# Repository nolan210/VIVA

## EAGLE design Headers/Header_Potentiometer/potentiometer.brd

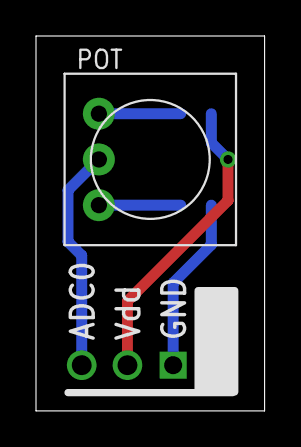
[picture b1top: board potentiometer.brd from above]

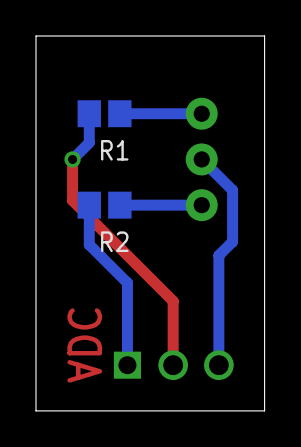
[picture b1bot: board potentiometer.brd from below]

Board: 2 copper layers, 12.7 x 20.8 mm, 4 parts (2 on the bottom side), 5 nets.

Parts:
POT: TRIM-3386
R1, R2: R0805
U$1: VIVA-HEADER-ADC-1; VIVA-HEADER-ADC-RA-2

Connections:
ADC: POT.2, U$1.3
GND: R2.1, U$1.1
unnamed: POT.1, R1.1
unnamed: POT.3, R2.2
VDD: R1.2, U$1.2

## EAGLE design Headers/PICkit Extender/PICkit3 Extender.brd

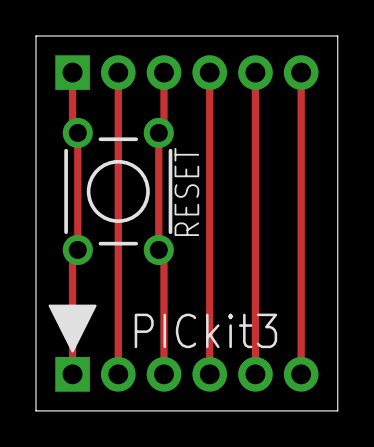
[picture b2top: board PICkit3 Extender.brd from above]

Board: 2 copper layers, 16.8 x 20.8 mm, 3 parts (0 on the bottom side), 6 nets.

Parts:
RESET: TL1105
U$1: PICKIT3; PINS_6_PICKIT3
U$3: PICKIT3PLAIN; PINS_6

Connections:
unnamed: RESET.2, RESET.4, U$1.1, U$3.1
unnamed: U$1.2, U$3.2
unnamed: RESET.1, RESET.3, U$1.3, U$3.3
unnamed: U$1.4, U$3.4
unnamed: U$1.5, U$3.5
unnamed: U$1.6, U$3.6

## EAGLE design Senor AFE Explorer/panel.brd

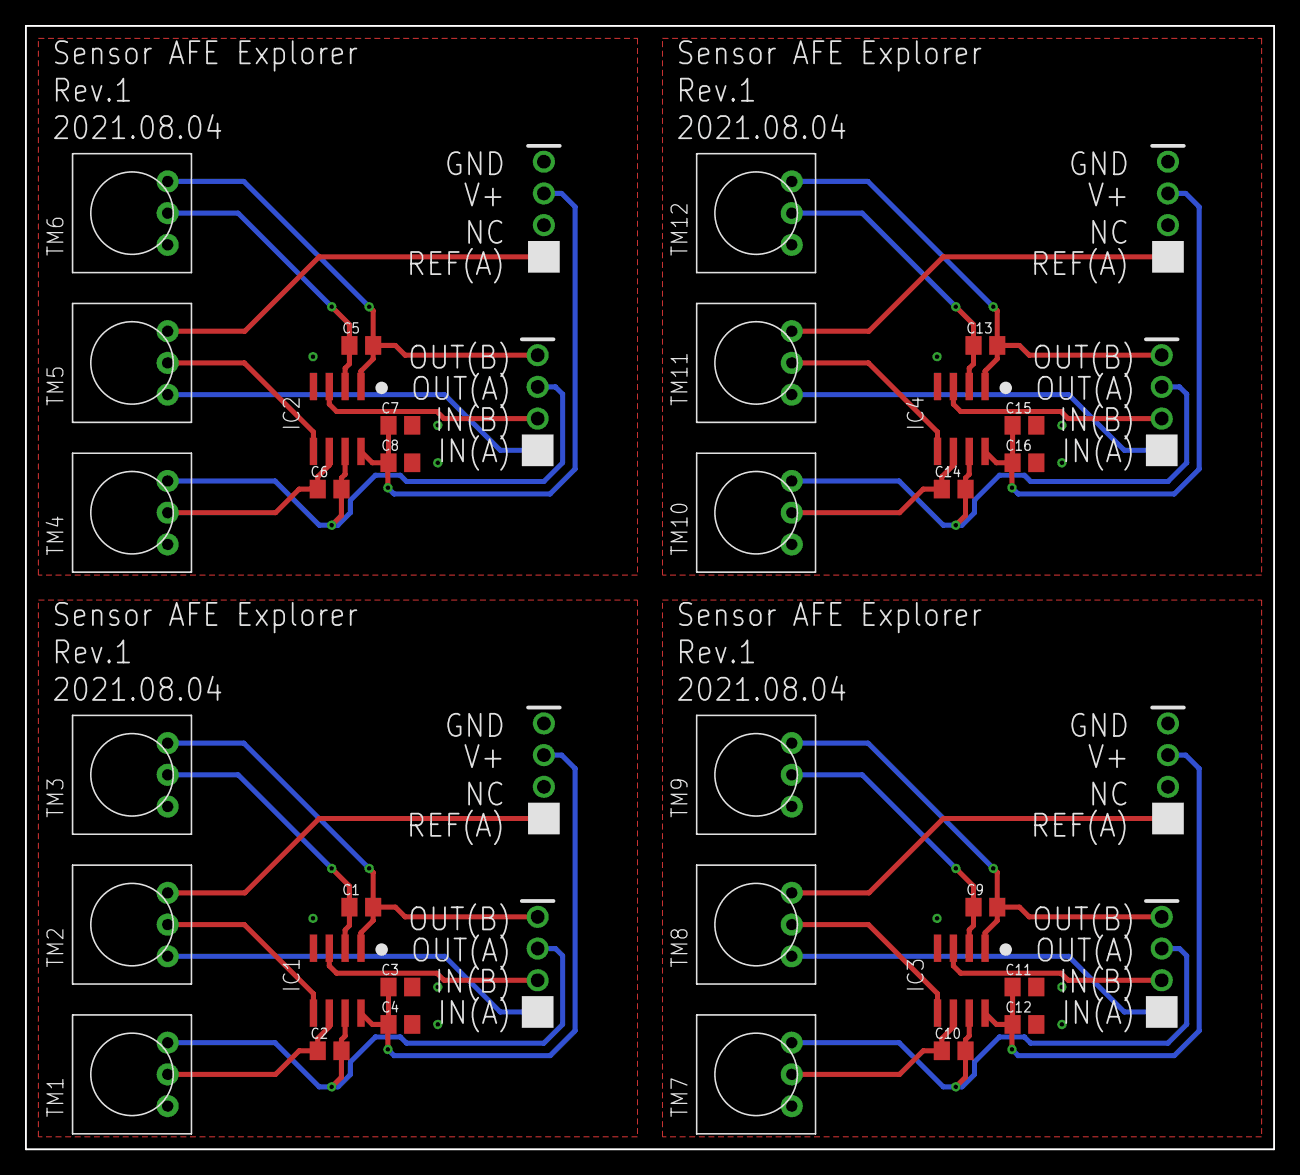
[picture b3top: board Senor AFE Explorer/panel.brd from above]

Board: 2 copper layers, 100.0 x 90.0 mm, 40 parts (0 on the bottom side), 40 nets.

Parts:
C1, C2, C3, C4, C5, C6, C7, C8, C9, C10, C11, C12, C13, C14, C15, C16: C0805
IC1, IC2, IC3, IC4: AD8542R; SO8
TM1, TM2, TM3, TM4, TM5, TM6, TM7, TM8, TM9, TM10, TM11, TM12: TRIM-3386
U$1, U$2, U$3, U$4, U$5, U$6, U$7, U$8: PINS_4SILK; PCB_4

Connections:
GND: C3.2, C4.2, IC1.4, TM1.1, TM3.1, U$2.P$4
GND1: C7.2, C8.2, IC2.4, TM4.1, TM6.1, U$4.P$4
GND2: C11.2, C12.2, IC3.4, TM7.1, TM9.1, U$6.P$4
GND3: C15.2, C16.2, IC4.4, TM10.1, TM12.1, U$8.P$4
unnamed: C2.1, IC1.6, TM1.2
unnamed: C2.2, IC1.7, TM1.3, U$1.P$3
unnamed: C1.1, IC1.2, TM3.2
unnamed: C1.2, IC1.1, TM3.3, U$1.P$4
unnamed: IC1.3, U$1.P$2
unnamed: TM2.1, U$1.P$1
unnamed: IC1.5, TM2.2
unnamed: TM2.3, U$2.P$1
unnamed: C6.1, IC2.6, TM4.2
unnamed: C6.2, IC2.7, TM4.3, U$3.P$3
unnamed: C5.1, IC2.2, TM6.2
unnamed: C5.2, IC2.1, TM6.3, U$3.P$4
unnamed: IC2.3, U$3.P$2
unnamed: TM5.1, U$3.P$1
unnamed: IC2.5, TM5.2
unnamed: TM5.3, U$4.P$1
unnamed: C10.1, IC3.6, TM7.2
unnamed: C10.2, IC3.7, TM7.3, U$5.P$3
unnamed: C9.1, IC3.2, TM9.2
unnamed: C9.2, IC3.1, TM9.3, U$5.P$4
unnamed: IC3.3, U$5.P$2
unnamed: TM8.1, U$5.P$1
unnamed: IC3.5, TM8.2
unnamed: TM8.3, U$6.P$1
unnamed: C14.1, IC4.6, TM10.2
unnamed: C14.2, IC4.7, TM10.3, U$7.P$3
unnamed: C13.1, IC4.2, TM12.2
unnamed: C13.2, IC4.1, TM12.3, U$7.P$4
unnamed: IC4.3, U$7.P$2
unnamed: TM11.1, U$7.P$1
unnamed: IC4.5, TM11.2
unnamed: TM11.3, U$8.P$1
VCC: C3.1, C4.1, IC1.8, U$2.P$3
VCC1: C7.1, C8.1, IC2.8, U$4.P$3
VCC2: C11.1, C12.1, IC3.8, U$6.P$3
VCC3: C15.1, C16.1, IC4.8, U$8.P$3

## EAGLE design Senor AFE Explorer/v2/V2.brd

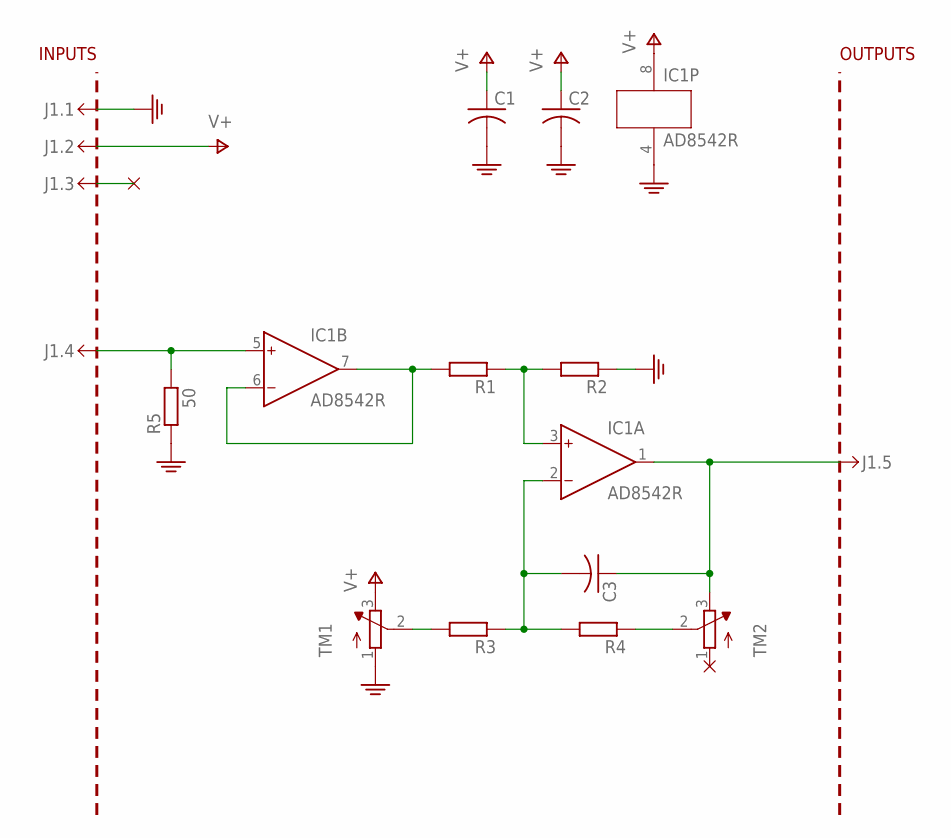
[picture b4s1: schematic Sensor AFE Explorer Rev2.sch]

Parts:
C1, C2, C3: C-USC0805; C0805
IC1: AD8542R; SO8
J1.: MINIPCB_5P50X50; MINIPCB_50X50MM; PART_NUMBER AFE Explorer
R1, R2, R3, R4: RESISTORSMD; R0805
R5: 50; R0805
TM1, TM2: TRIMPOT3386; TRIM-3386

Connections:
GND: C1.2, C2.2, IC1.4 (V-), J1..1, R2.1, R5.1, TM1.1 (A)
unnamed: IC1.5 (IN+), J1..4, R5.2
unnamed: IC1.6 (IN-), IC1.7 (OUT), R1.2
unnamed: IC1.3 (IN+), R1.1, R2.2
unnamed: C3.2, IC1.2 (IN-), R3.1, R4.2
unnamed: R3.2, TM1.2 (S)
unnamed: R4.1, TM2.2 (S)
unnamed: C3.1, IC1.1 (OUT), J1..5, TM2.3 (E)
V+: C1.1, C2.1, IC1.8 (V+), J1..2, TM1.3 (E)

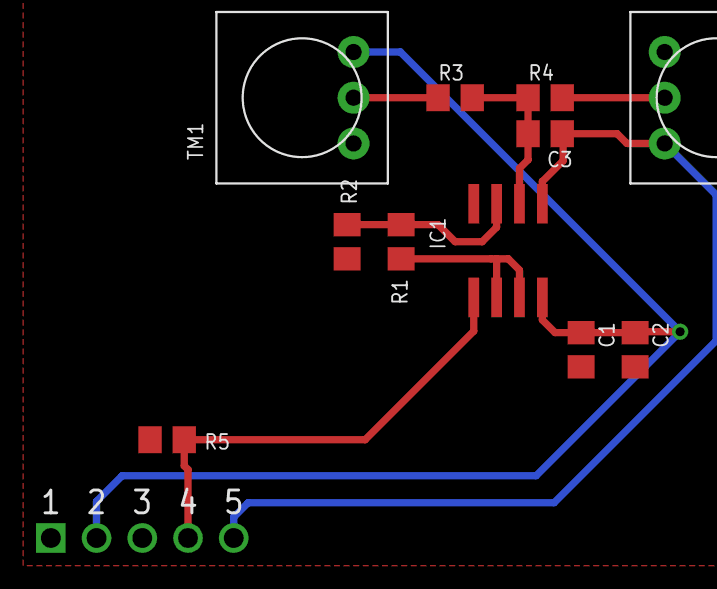
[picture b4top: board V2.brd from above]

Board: 2 copper layers, 12 parts (0 on the bottom side), 9 nets.

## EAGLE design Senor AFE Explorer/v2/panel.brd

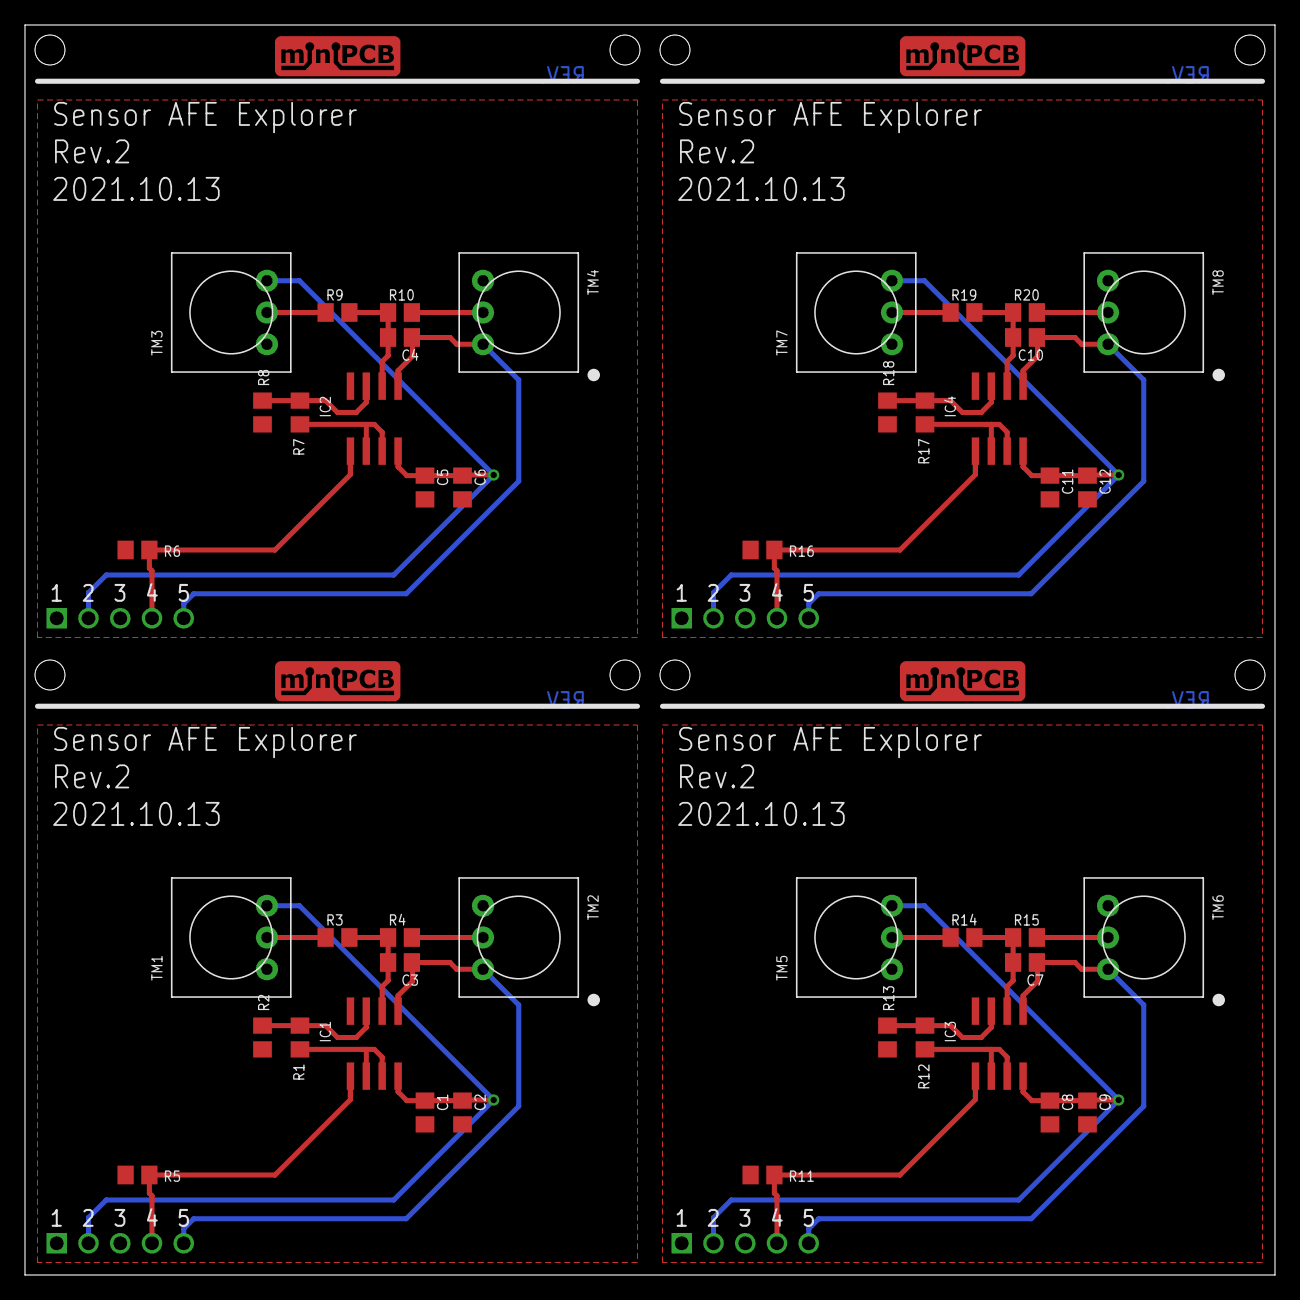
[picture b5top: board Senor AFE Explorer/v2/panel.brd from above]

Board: 2 copper layers, 100.0 x 100.0 mm, 48 parts (0 on the bottom side), 36 nets.

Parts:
C1, C2, C3, C4, C5, C6, C7, C8, C9, C10, C11, C12: C0805
IC1, IC2, IC3, IC4: AD8542R; SO8
J1., J1.1, J1.2, J1.3: MINIPCB_50X50MM
R1, R2, R3, R4, R7, R8, R9, R10, R12, R13, R14, R15, R17, R18, R19, R20: R0805
R5, R6, R11, R16: 50; R0805
TM1, TM2, TM3, TM4, TM5, TM6, TM7, TM8: TRIM-3386

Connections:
GND: C1.2, C2.2, IC1.4, J1..1, R2.1, R5.1, TM1.1
GND1: C5.2, C6.2, IC2.4, J1.1.1, R6.1, R8.1, TM3.1
GND2: C8.2, C9.2, IC3.4, J1.2.1, R11.1, R13.1, TM5.1
GND3: C11.2, C12.2, IC4.4, J1.3.1, R16.1, R18.1, TM7.1
unnamed: IC1.5, J1..4, R5.2
unnamed: IC1.6, IC1.7, R1.2
unnamed: IC1.3, R1.1, R2.2
unnamed: C3.2, IC1.2, R3.1, R4.2
unnamed: R3.2, TM1.2
unnamed: C3.1, IC1.1, J1..5, TM2.3
unnamed: R4.1, TM2.2
unnamed: IC2.5, J1.1.4, R6.2
unnamed: IC2.6, IC2.7, R7.2
unnamed: IC2.3, R7.1, R8.2
unnamed: C4.2, IC2.2, R9.1, R10.2
unnamed: R9.2, TM3.2
unnamed: C4.1, IC2.1, J1.1.5, TM4.3
unnamed: R10.1, TM4.2
unnamed: IC3.5, J1.2.4, R11.2
unnamed: IC3.6, IC3.7, R12.2
unnamed: IC3.3, R12.1, R13.2
unnamed: C7.2, IC3.2, R14.1, R15.2
unnamed: R14.2, TM5.2
unnamed: C7.1, IC3.1, J1.2.5, TM6.3
unnamed: R15.1, TM6.2
unnamed: IC4.5, J1.3.4, R16.2
unnamed: IC4.6, IC4.7, R17.2
unnamed: IC4.3, R17.1, R18.2
unnamed: C10.2, IC4.2, R19.1, R20.2
unnamed: R19.2, TM7.2
unnamed: C10.1, IC4.1, J1.3.5, TM8.3
unnamed: R20.1, TM8.2
V+: C1.1, C2.1, IC1.8, J1..2, TM1.3
V+1: C5.1, C6.1, IC2.8, J1.1.2, TM3.3
V+2: C8.1, C9.1, IC3.8, J1.2.2, TM5.3
V+3: C11.1, C12.1, IC4.8, J1.3.2, TM7.3

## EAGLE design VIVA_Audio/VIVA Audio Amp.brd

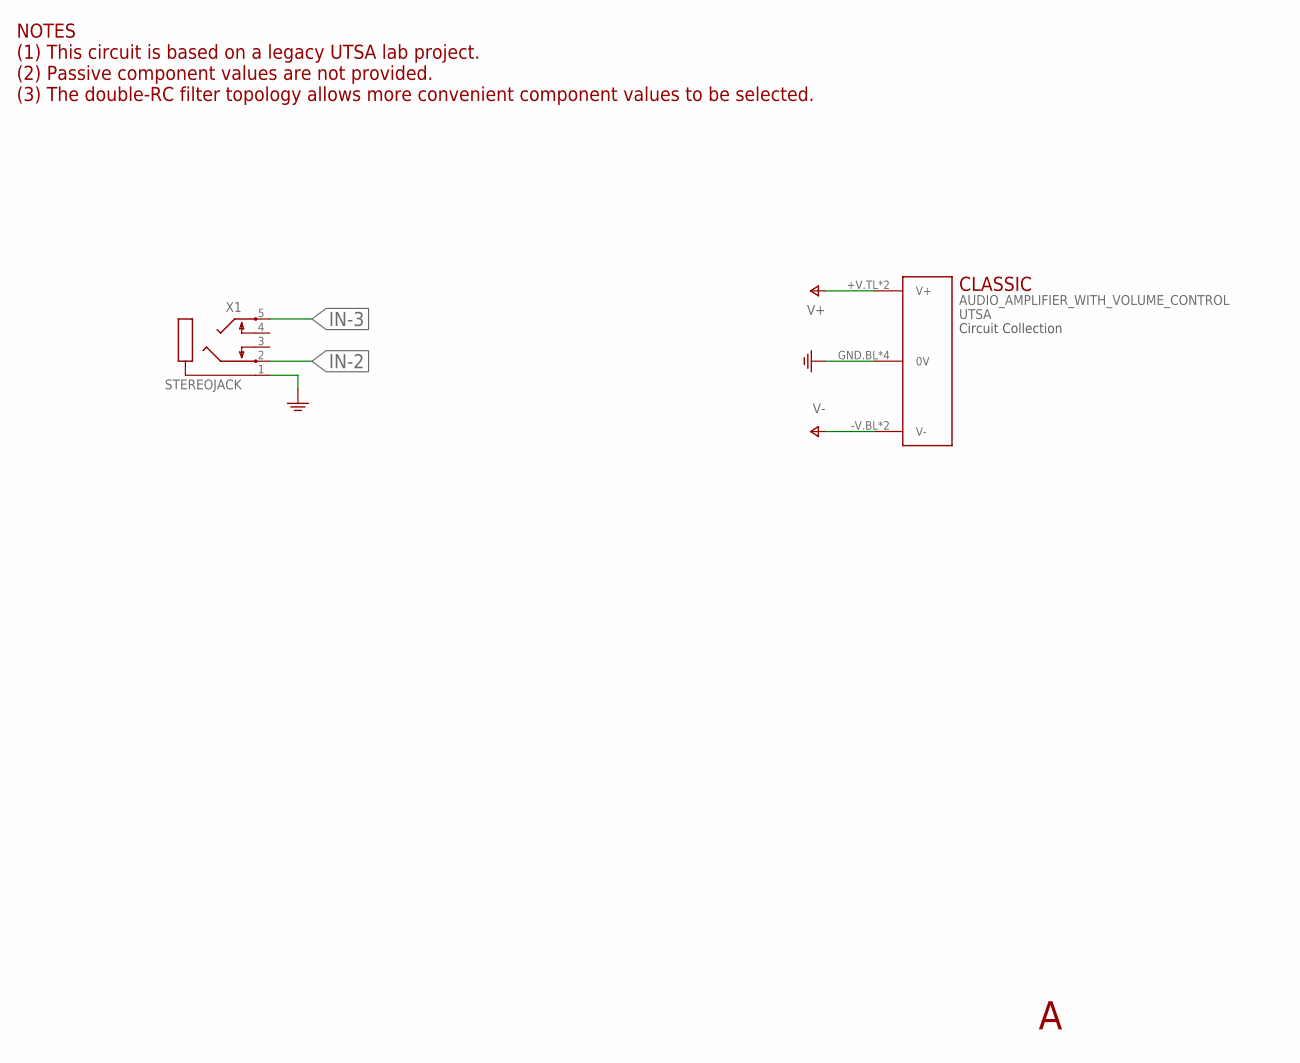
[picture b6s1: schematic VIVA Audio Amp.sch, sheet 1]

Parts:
AUDIO_AMPLIFIER_WITH_VOLUME_CONTROL: UTSA; CLASSIC_3-5"
X1: STEREOJACK; STX3100

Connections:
GND: AUDIO_AMPLIFIER_WITH_VOLUME_CONTROL.GND.BL (0V), AUDIO_AMPLIFIER_WITH_VOLUME_CONTROL.GND.BR (0V), AUDIO_AMPLIFIER_WITH_VOLUME_CONTROL.GND.TL (0V), AUDIO_AMPLIFIER_WITH_VOLUME_CONTROL.GND.TR (0V), X1.1; also elsewhere on the board
IN-2: X1.2; also elsewhere on the board
IN-3: X1.5; also elsewhere on the board
V+: AUDIO_AMPLIFIER_WITH_VOLUME_CONTROL.+V.TL (V+), AUDIO_AMPLIFIER_WITH_VOLUME_CONTROL.+V.TR (V+); also elsewhere on the board
V-: AUDIO_AMPLIFIER_WITH_VOLUME_CONTROL.-V.BL (V-), AUDIO_AMPLIFIER_WITH_VOLUME_CONTROL.-V.BR (V-); also elsewhere on the board

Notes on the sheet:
NOTES (1) This circuit is based on a legacy UTSA lab project. (2) Passive component values are not provided. (3) The double-RC filter topology allows more convenient component values to be selected.

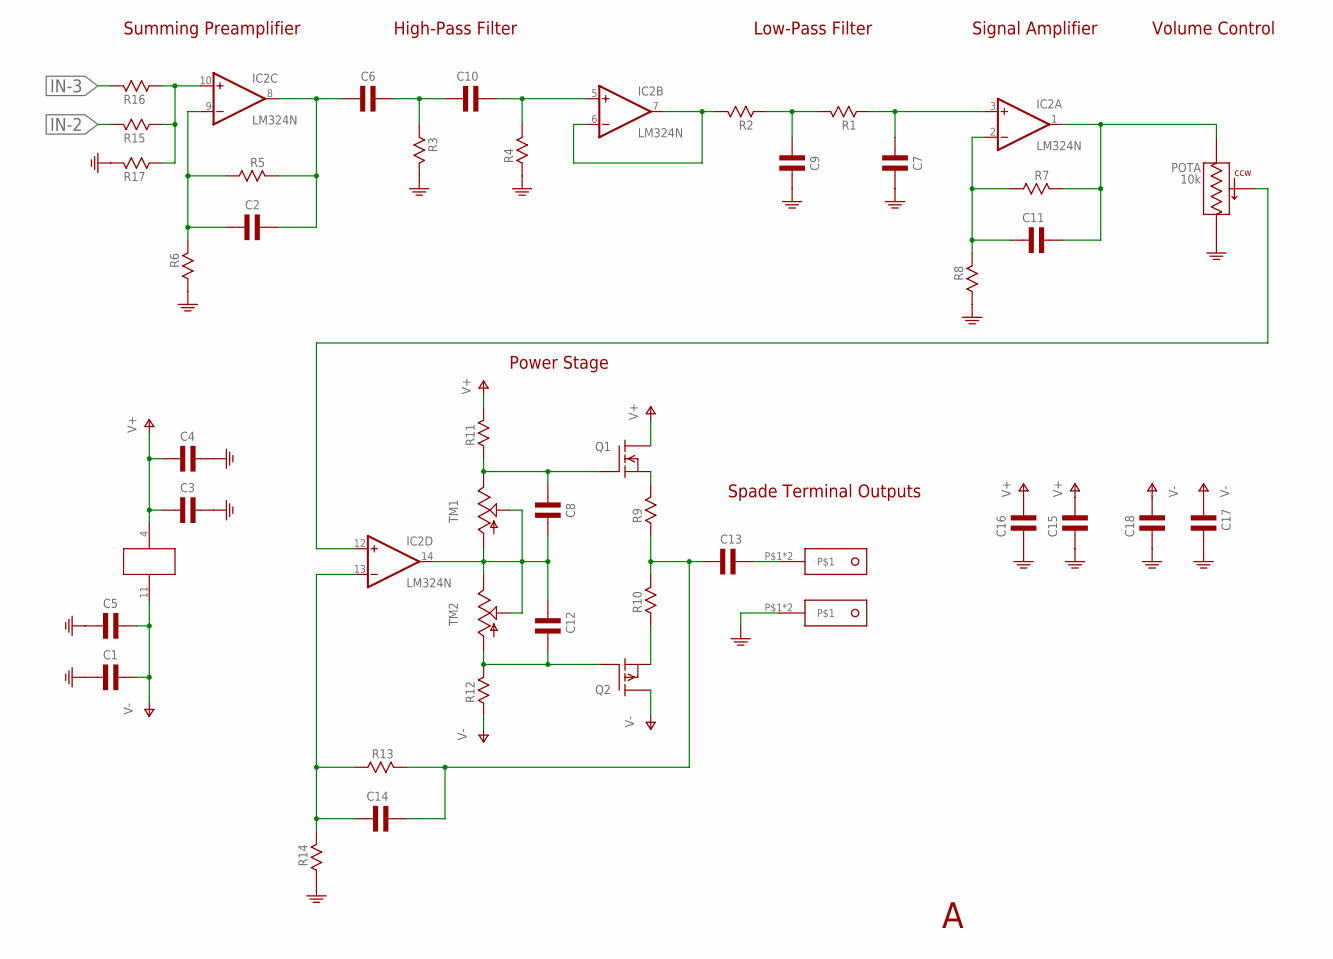
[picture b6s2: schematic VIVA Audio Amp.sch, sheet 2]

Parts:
C1, C2, C3, C6, C7, C8, C9, C10, C11, C12, C14, C16, C18: COVAL; C050-024X044
C4, C5, C15, C17: C2.5-10; E2,5-5
C13: C3.5-10; E3,5-10
IC2: LM324N; DIL14
POT: 10k; WH148
Q1: N-MOSFETTO220V; TO220V
Q2: P-MOSFETTO220V; TO220V
R1, R2, R3, R4, R5, R6, R7, R8, R9, R10, R11, R12, R13, R14, R15, R16, R17: R204-7; 0204/7
TM1, TM2: TRIM6MM; 6MM
U$2, U$3: SPADE-TAB; SPADE-TAB-6.3MM

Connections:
GND: C1.1, C3.2, C4.-, C5.+, C7.1, C9.1, C15.-, C16.2, C17.+, C18.2, POT.4.FL (1.L), R3.2, R4.1, R6.2, R8.2, R14.2, R17.1, U$3.P$1, U$3.P$2; also elsewhere on the board
IN-2: R15.1; also elsewhere on the board
IN-3: R16.1; also elsewhere on the board
INPUT: IC2.10 (+IN), R15.2, R16.2, R17.2
unnamed: C9.2, R1.2, R2.1
unnamed: C2.2, IC2.9 (-IN), R5.2, R6.1
unnamed: C2.1, C6.2, IC2.8 (OUT), R5.1
unnamed: C7.2, IC2.3 (+IN), R1.1
unnamed: IC2.6 (-IN), IC2.7 (OUT), R2.2
unnamed: Q2.3 (S), R10.1
unnamed: C10.1, IC2.5 (+IN), R4.2
unnamed: C6.1, C10.2, R3.1
unnamed: C11.1, IC2.1 (OUT), POT.6.FR (3.R), R7.1
unnamed: C11.2, IC2.2 (-IN), R7.2, R8.1
unnamed: C8.2, Q1.1 (G), R11.1, TM1.E
unnamed: C12.1, Q2.1 (G), R12.2, TM2.A
unnamed: C13.+, C14.1, R9.1, R10.2, R13.1
unnamed: Q1.3 (S), R9.2
unnamed: C13.-, U$2.P$1, U$2.P$2
unnamed: IC2.12 (+IN), POT.5.FC (2.C)
unnamed: C14.2, IC2.13 (-IN), R13.2, R14.1
unnamed: C8.1, C12.2, IC2.14 (OUT), TM1.A, TM1.S, TM2.E, TM2.S
V+: C3.1, C4.+, C15.+, C16.1, IC2.4 (V+), Q1.2 (D), R11.2; also elsewhere on the board
V-: C1.2, C5.-, C17.-, C18.1, IC2.11 (V-), Q2.2 (D), R12.1; also elsewhere on the board

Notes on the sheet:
Summing Preamplifier
High-Pass Filter
Low-Pass Filter
Signal Amplifier
Volume Control
Power Stage
Spade Terminal Outputs

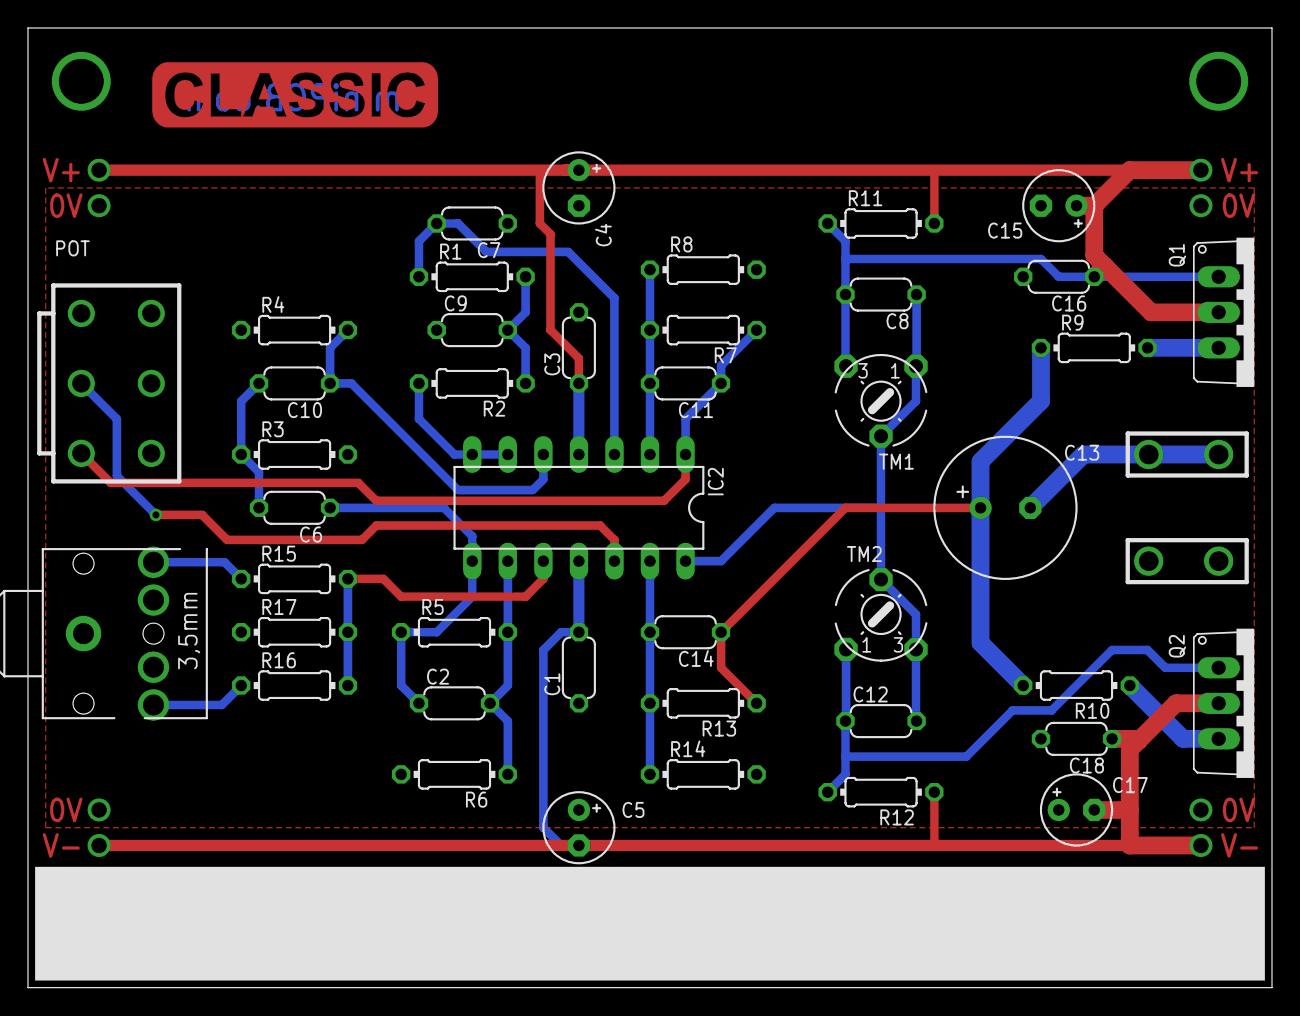
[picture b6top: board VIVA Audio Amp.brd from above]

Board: 2 copper layers, 88.9 x 68.6 mm, 45 parts (0 on the bottom side), 24 nets.

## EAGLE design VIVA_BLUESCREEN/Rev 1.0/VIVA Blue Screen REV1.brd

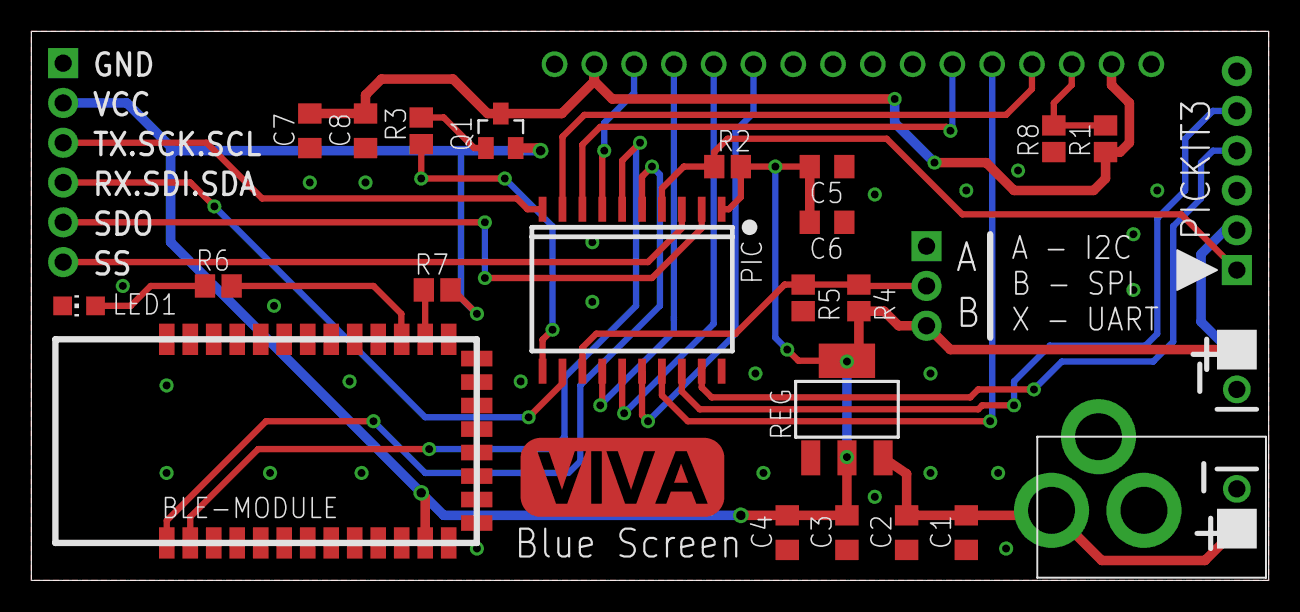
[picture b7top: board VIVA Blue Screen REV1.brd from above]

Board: 2 copper layers, 79.0 x 35.1 mm, 29 parts (1 on the bottom side), 27 nets.

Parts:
BLE-MODULE: HM-10
C1, C2, C3, C4, C5, C6, C7, C8: C0805
J1: 2.1MMJACKTHM; PJ-102A
J3: PICKIT3; PINS_6_PICKIT3
LED1: CHIP-LED0805
PIC: PIC16F1829; SOP20-NEW
Q1: PNP; SOT23
R1, R3, R4, R5, R8: R0805
R2, R6, R7: 10k; R0805
REG: SOT223
U$1: PINS_3
U$2, U$9: PCB_2
U$3: PINS_6SQUARE; PINS_6
U$4: VIVA_LOGO
X1: HD44780LCD-VIVA; LCD1602-VIVA

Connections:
+V: BLE-MODULE.12, C3.2, C4.2, C5.2, C6.2, J3.2, PIC.1, Q1.2, R2.2, R4.2, R7.1, REG.2, REG.4, U$1.3, U$3.2, U$9.P$1
BLE.KEY: BLE-MODULE.23, R7.2
BLE.LED: BLE-MODULE.24, R6.2
BLE.RX: BLE-MODULE.2, PIC.6
BLE.TX: BLE-MODULE.1, PIC.5
CLK: J3.5, PIC.18
DAT: J3.4, PIC.19
GND: BLE-MODULE.13, BLE-MODULE.14, BLE-MODULE.21, BLE-MODULE.22, C1.1, C2.1, C3.1, C4.1, C5.1, C6.1, C7.1, C8.1, J1.RING, J3.3, LED1.C, PIC.20, R5.2, R8.2, REG.1, U$1.1, U$2.P$3, U$3.1, U$9.P$3, X1.1, X1.16
LCD.D4: PIC.16, X1.11
LCD.D5: PIC.15, X1.12
LCD.D6: PIC.14, X1.13
LCD.D7: PIC.7, X1.14
LCD.E: PIC.8, X1.6
LCD.RS: PIC.9, X1.4
LCD.RW: PIC.17, X1.5
LCD_+V: C7.2, C8.2, Q1.3, R1.1, X1.2, X1.15
LCD_CON: PIC.11, R3.1
MCLR: J3.1, PIC.4, R2.1
unnamed: C1.2, C2.2, J1.TIP, REG.3, U$2.P$1
unnamed: LED1.A, R6.1
unnamed: Q1.1, R3.2
RB4: PIC.13, R4.1, R5.1, U$1.2
RX.SDI.SDA: PIC.12, U$3.4
SDO: PIC.2, U$3.5
SS: PIC.3, U$3.6
TX.SCK.SCL: PIC.10, U$3.3
VO: R1.2, R8.1, X1.3
